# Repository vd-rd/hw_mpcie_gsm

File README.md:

## Overview
Open Hardware Mini PCI Express GPS module for embedded communications or DIY projects.

### Specifications
 * Simcom SIM800 GSM modem

### Features
 * Compliant with the half mPCI Express mechanical and electrical specifications (rev 2.1)
 * Relatively easy to assemble at home (some experience with SMD soldering required)
 * No special driver required under Linux (exposed as CDC interface)
 * Separate .1inch breakout header for UART interfacing
 * Compliant with most cheap mPCI to USB solutions

### Resources
You can find all necesary information to build or evaluate the module here:
   - [View 3D board render](https://a360.co/2J9JpYO)
   - [Fabrication files](https://github.com/vd-rd/hw_mpcie_gsm/releases)

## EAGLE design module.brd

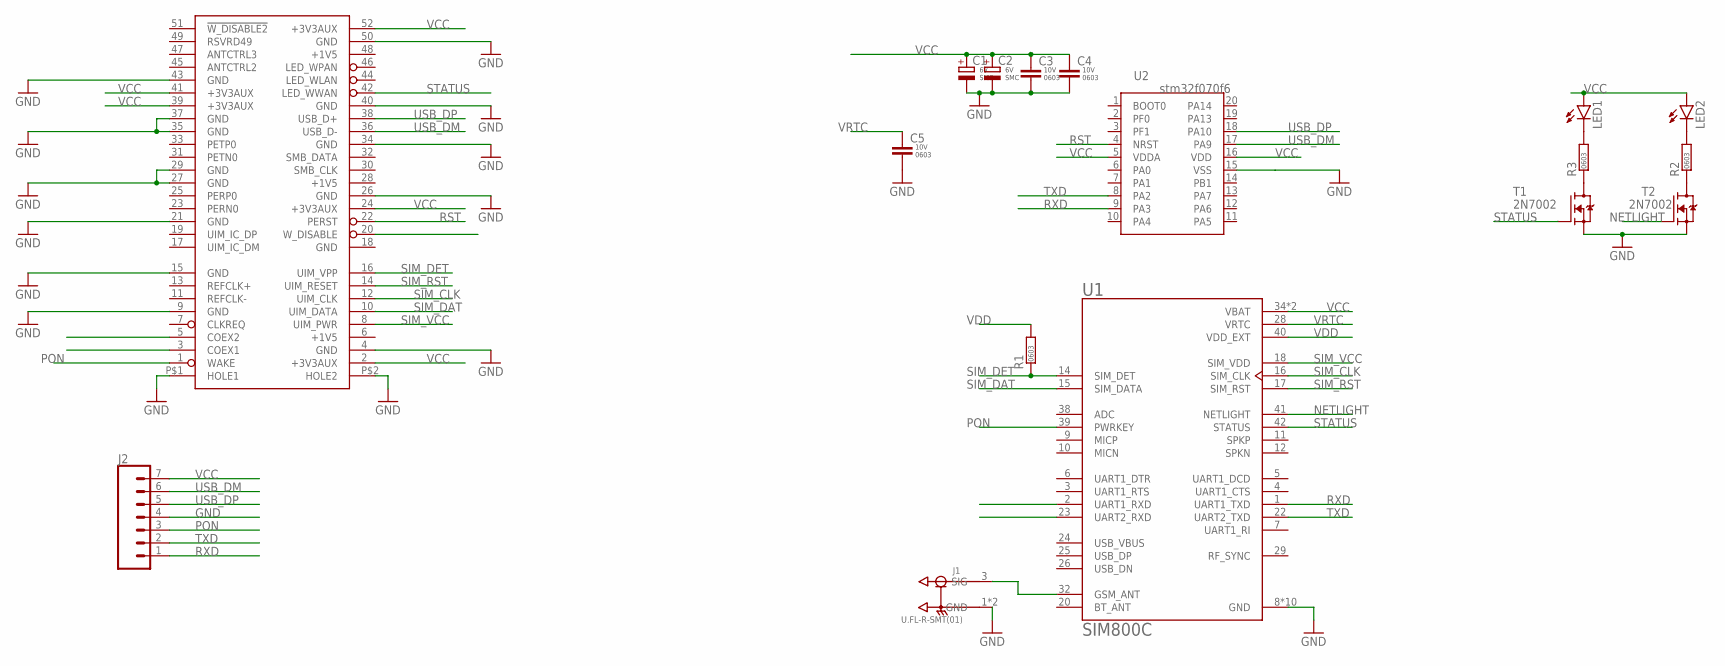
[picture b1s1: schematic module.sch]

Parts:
C1, C2: CAP-POL-SMC; SMC_C
C3, C4, C5: CAP-0603; C0603
FORM1: MPCIE_HALF
J1: U.FL-R-SMT(01); HRS_U.FL-R-SMT(01)
J2: CONN_07; 1X07
LED1, LED2: LEDCHIP-LED0603; CHIP-LED0603
R1, R2, R3: RES-0603; R0603
T1, T2: 2N7002; SOT95P240X110-3
U1: SIM800C; LCC110P1570X1760X250-42N
U2: STM32F070F6; SOP65P640X120-20

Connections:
+1V5: FORM1.6 (+1V5), FORM1.28 (+1V5)
GND: C1.-, C2.-, C3.2, C4.2, C5.2, FORM1.4 (GND), FORM1.9 (GND), FORM1.15 (GND), FORM1.18 (GND), FORM1.21 (GND), FORM1.26 (GND), FORM1.27 (GND), FORM1.29 (GND), FORM1.34 (GND), FORM1.35 (GND), FORM1.37 (GND), FORM1.40 (GND), FORM1.43 (GND), FORM1.50 (GND), FORM1.P$1 (HOLE1), FORM1.P$2 (HOLE2), J1.1 (GND), J1.2 (GND), J2.4, T1.2 (S), T2.2 (S), U1.8 (GND), U1.13 (GND), U1.19 (GND), U1.21 (GND), U1.27 (GND), U1.30 (GND), U1.31 (GND), U1.33 (GND), U1.36 (GND), U1.37 (GND), U2.15 (VSS)
unnamed: J1.3 (SIG), U1.32 (GSM_ANT)
unnamed: LED2.C, R2.2
unnamed: LED1.C, R3.2
unnamed: R3.1, T1.3 (D)
unnamed: R2.1, T2.3 (D)
NETLIGHT: T2.1 (G), U1.41 (NETLIGHT)
PON: FORM1.1 (WAKE), J2.3, U1.39 (PWRKEY)
RST: FORM1.22 (PERST), U2.4 (NRST)
RXD: J2.1, U1.1 (UART1_TXD), U2.9 (PA3)
SIM_CLK: FORM1.12 (UIM_CLK), U1.16 (SIM_CLK)
SIM_DAT: FORM1.10 (UIM_DATA), U1.15 (SIM_DATA)
SIM_DET: FORM1.16 (UIM_VPP), R1.1, U1.14 (SIM_DET)
SIM_RST: FORM1.14 (UIM_RESET), U1.17 (SIM_RST)
SIM_VCC: FORM1.8 (UIM_PWR), U1.18 (SIM_VDD)
SMB_DATA: FORM1.32 (SMB_DATA)
STATUS: FORM1.42 (LED_WWAN), T1.1 (G), U1.42 (STATUS)
TXD: J2.2, U1.22 (UART2_TXD), U2.8 (PA2)
USB_DM: FORM1.36 (USB_D-), J2.6, U2.17 (PA9)
USB_DP: FORM1.38 (USB_D+), J2.5, U2.18 (PA10)
VCC: C1.+, C2.+, C3.1, C4.1, FORM1.2 (+3V3AUX), FORM1.24 (+3V3AUX), FORM1.39 (+3V3AUX), FORM1.41 (+3V3AUX), FORM1.52 (+3V3AUX), J2.7, LED1.A, LED2.A, U1.34 (VBAT), U1.35 (VBAT), U2.5 (VDDA), U2.16 (VDD)
VDD: R1.2, U1.40 (VDD_EXT)
VRTC: C5.1, U1.28 (VRTC)

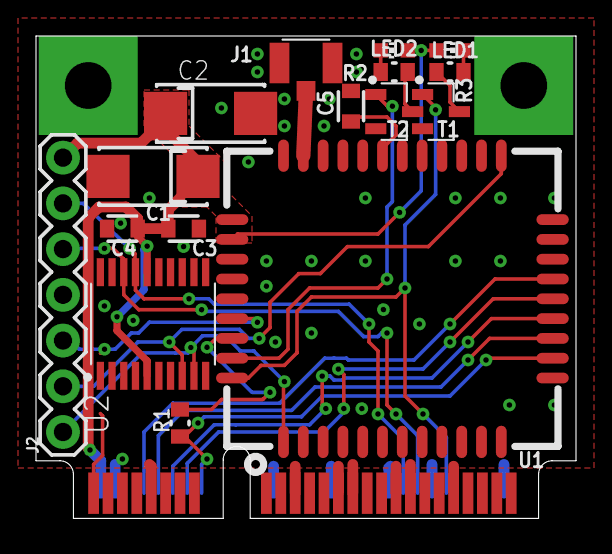
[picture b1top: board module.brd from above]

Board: 2 copper layers, 30.0 x 26.8 mm, 17 parts (0 on the bottom side), 23 nets.

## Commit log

2019-05-02 project: add cad files

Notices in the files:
parts and their libraries:
SparkFun-Connectors: Licensing: Creative Commons ShareAlike 4.0 International - https://creativecommons.org/licenses/by-sa/4.0
